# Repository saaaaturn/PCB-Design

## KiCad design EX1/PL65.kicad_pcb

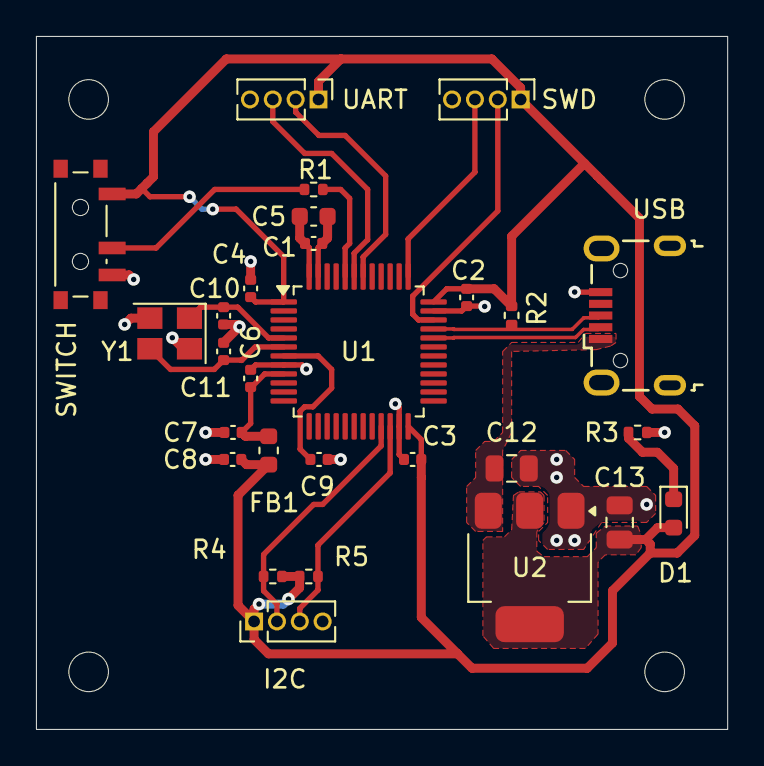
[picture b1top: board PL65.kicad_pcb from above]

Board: 2 copper layers, 38.4 x 38.5 mm, 32 parts (0 on the bottom side), 18 nets.

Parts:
C1, C2, C3, C4, C9: 100n; C_0402_1005Metric
C5: 10u; C_0603_1608Metric
C6: 10n; C_0402_1005Metric
C7, C8: 1u; C_0402_1005Metric
C10, C11: 10pF; C_0402_1005Metric
C12, C13: 22u; C_0805_2012Metric
D1: LED; LED_0603_1608Metric
FB1: 120R; L_0603_1608Metric
H1, H2, H3, H4: MountingHole; MountingHole_2.2mm_M2
I2C: Conn_01x04_Pin; PinHeader_1x04_P1.27mm_Vertical
R1: 10k; R_0402_1005Metric
R2, R3, R4, R5: 1k5; R_0402_1005Metric
SWD: Conn_01x04_Pin; PinHeader_1x04_P1.27mm_Vertical
SWITCH: SW_SPDT; SW_SPDT_PCM12
U1: STM32F103C8Tx; LQFP-48_7x7mm_P0.5mm
U2: AMS1117-3.3; SOT-223-3_TabPin2
UART: Conn_01x04_Pin; PinHeader_1x04_P1.27mm_Vertical
USB: USB_B_Micro; USB_Micro-B_Wuerth_629105150521
Y1: 16MHz; Crystal_SMD_3225-4Pin_3.2x2.5mm

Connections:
+3.3V: C1.2, C2.2, C3.2, C4.2, C5.2, C8.2, C13.2, D1.2 (A), FB1.2, I2C.1, R2.1, R4.1, R5.1, SWD.1, SWITCH.1 (A), U1.1 (VBAT), U1.24 (VDD), U1.36 (VDD), U1.48 (VDD), U2.2 (VO), UART.1
+3.3VA: C6.2, C7.2, FB1.1, U1.9 (VDDA)
/BOOT0: R1.2, U1.44 (BOOT0)
/HSE_IN: C10.1, U1.5 (PD0), Y1.1
/HSE_OUT: C11.1, U1.6 (PD1), Y1.3
/NRST: C9.2, U1.7 (NRST)
/PW_LED: D1.1 (K), R3.2
/SWCLK: SWD.3, U1.37 (PA14)
/SWDIO: SWD.2, U1.34 (PA13)
/SW_BOOT0: R1.1, SWITCH.2 (B)
/USB_D+: R2.2, U1.33 (PA12), USB.3 (D+)
/USB_D-: U1.32 (PA11), USB.2 (D-)
GND: C1.1, C2.1, C3.1, C4.1, C5.1, C6.1, C7.1, C8.1, C9.1, C10.2, C11.2, C12.1, C13.1, I2C.4, R3.1, SWD.4, SWITCH.3 (C), U1.8 (VSSA), U1.23 (VSS), U1.35 (VSS), U1.47 (VSS), U2.1 (GND), UART.4, USB.5 (GND), Y1.2, Y1.4
unnamed: U1.42 (PB6), UART.2
unnamed: U1.43 (PB7), UART.3
unnamed: I2C.2, R4.2, U1.21 (PB10)
unnamed: I2C.3, R5.2, U1.22 (PB11)
VBUS: C12.2, U2.3 (VI), USB.1 (VBUS)

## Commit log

2024-08-25 Create A
